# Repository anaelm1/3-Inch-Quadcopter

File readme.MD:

# 3-Inch Quadcopter

The quadcopter is a beginner-friendly drone built with a custom PCB and a custom 3D-printed body. 

The inspiration behind this project was to reignite the interest in drones I had when I was younger, and it will also be as a showcase project for my intended majors (mechanical and aeronautical engineering). Beyond this, the project is part of a idea of building autonomous delivery drones.

## Features
-  Custom PCB featuring an ESP32-C3 development board and a GY-521 IMU (gyroscope/accelerometer).
- Uses high-efficiency MOSFETs to drive the motors.
- Fully controllable via smartphone using the official ESP-Drone application over Wi-Fi.
- Designed with a 2:1 thrust-to-weight ratio to allow for snappy punch-outs.
- Balanced 3D-printed PETG X frame.

## CAD Model
The PCB is secured to the base plate using four M3 screws, with the battery fastened underneath using a Velcro strap. Cutouts on the base plate act as heat sinks for the MOSFETs. My name is embossed on the top plate.

*Designed in Autodesk Fusion 360.*

## PCB
The custom PCB was designed in KiCad. Power traces are wider  to safely handle high current loads. The board dimensions are 70mm × 70mm cuz I avoided surface mount components.

### Schematic

### PCB Layout

### 3D Render

## Firmware Overview
The firmware is written in the Arduino IDE. It implements a deterministic PID control loop and Wi-Fi initialization to work with the ESP-Drone mobile app.

## AI Usage
While I tried to keep AI use to a minimum, AI tools were utilized for:
- Researching and finalizing all electronic components.
- Helping with the firmware architecture.

## Experience
Building this project has been an incredible learning experience. I gained knowledge abou power electronics e.g capacitors, MOSFETs, and circuit protection. There were multiple design pivots throughout the development process (documented in `journal.md`). What I originally planned as a straightforward wiring exercise of connecting motors, an ESP32-C3, and a gyro truned into designing a detailed, PCB with over 30 components. Learning how to read manufacturer datasheets and apply them directly to hardware design was one of the most valuable takeaways of the project.

---

## Bill of Materials (BOM)

| Part | Type | Quantity | Unit price (USD) | Line total (USD) | Link | Vendor | Funding | Notes | CART |
| :--- | :--- | :---: | :---: | :---: | :--- | :--- | :--- | :--- | :--- |
| XT30U Male/Female Connectors (5 Pairs) | Part | 1 | $1.12 | $1.12 | https://s.click.aliexpress.com/e/_c3889eTv | Shop1105163493 Store | Grant | | AliExpress |
| 1W Metal Film Resistor 100 Ohm (20pcs pack) | Part | 1 | $1.97 | $1.97 | https://s.click.aliexpress.com/e/_c3E3aj0J | FXI Electronics Co. Ltd. Store | Grant | Lowest quantity sold together | AliExpress |
| 1W Metal Film Resistor 4.7K Ohm (20pcs pack) | Part | 1 | $1.94 | $1.94 | https://s.click.aliexpress.com/e/_c4SeKWnt | FXI Electronics Co. Ltd. Store | Grant | Lowest quantity sold together | AliExpress |
| 1W Metal Film Resistor 1K Ohm (20pcs pack) | Part | 1 | $1.97 | $1.97 | https://s.click.aliexpress.com/e/_c3FJaONV | FXI Electronics Co. Ltd. Store | Grant | Lowest quantity sold together | AliExpress |
| 75mm 2-Blade Propellers 4 Pairs | Part | 1 | $2.40 | $2.40 | https://s.click.aliexpress.com/e/_c3Jr3oTh | RC Club Store | Grant | | AliExpress |
| M3x5mm Nylon Pan Head Screws (50pcs pack) | Part | 1 | $0.93 | $0.93 | https://www.aliexpress.com/item/1005003145381687.html?spm=a2g0o.cart.0.0.e6cc38daaiHVPw&mp=1&pdp_npi=6%40dis%21USD%21USD+0.98%21USD+0.93%21%21USD+0.93%21%21%21%400be71e1917946913243825978e105e%2112000024341162464%21ct%21PK%216665188549%21%211%210%21 | HZYUEGOU SCREWHOME Store | Grant | Lowest quantity sold together | AliExpress |
| 16V 470uF Electrolytic Capacitor (5pcs pack) | Part | 1 | $1.83 | $1.83 | https://s.click.aliexpress.com/e/_c3mb84rh | shenzhenYida Store | Grant | Lowest quantity sold together | AliExpress |
| 16V 47uF Electrolytic Capacitor (5pcs pack) | Part | 1 | $1.69 | $1.69 | https://s.click.aliexpress.com/e/_c3Ba7dwL | shenzhenYida Store | Grant | Lowest quantity sold together | AliExpress |
| ESP32-C3 SuperMini Development Board | Part | 1 | $2.96 | $2.96 | https://www.aliexpress.com/item/1005008815113485.html?spm=a2g0o.cart.0.0.e6cc38daaiHVPw&mp=1&pdp_npi=6%40dis%21USD%21USD+3.96%21USD+2.96%21%21USD+2.96%21%21%21%400be71e1917946913243825978e105e%2112000053564399094%21ct%21PK%216665188549%21%211%210%21 | Shop1104003965 Store | Grant | | AliExpress |
| SS54 SMA SMD Rectifier Diode (50pcs pack) | Part | 1 | $1.91 | $1.91 | https://s.click.aliexpress.com/e/_c3g7i4M7 | Shop1103320155 Store | Grant | Lowest quantity sold together | AliExpress |
| IRF3708 TO-220 N-Channel MOSFET (10pcs pack) | Part | 1 | $3.49 | $3.49 | https://s.click.aliexpress.com/e/_c3twfGQB | Shop1105738136 Store | Grant | Lowest quantity sold together | AliExpress |
| 100nF Monolithic Ceramic Capacitor (100pcs pack) | Part | 1 | $1.78 | $1.78 | https://www.aliexpress.com/item/1135571256.html?spm=a2g0o.cart.0.0.e6cc38daaiHVPw&mp=1&pdp_npi=6%40dis%21USD%21USD+2.03%21USD+1.78%21%21USD+1.78%21%21%21%400be71e1917946913282516061e105e%2165192300108%21ct%21PK%216665188549%21%211%210%21 | Chinese Super Electronic market | Grant | Lowest quantity sold together | AliExpress |
| 5mm Assorted LED Diode Kit (100pcs total) | Part | 1 | $2.40 | $2.40 | https://www.aliexpress.com/item/1005003395932705.html?spm=a2g0o.cart.0.0.e6cc38daaiHVPw&mp=1&pdp_npi=6%40dis%21USD%21USD+2.78%21USD+2.40%21%21USD+2.40%21%21%21%400be71e1917946913282516061e105e%2112000025597631785%21ct%21PK%216665188549%21%211%210%21 | Pingtoudidi Store | Grant | Lowest quantity sold together | AliExpress |
| 5x20mm PCB Fuse Holder + 10A Fuse (10pcs pack) | Part | 1 | $2.15 | $2.15 | https://s.click.aliexpress.com/e/_c3f8mbJ5 | Ali_CanHui Store | Grant | Lowest quantity sold together | AliExpress |
| 1020 Coreless Motor 3.7V 54000RPM (2pcs pack) | Part | 3 | $3.70 | $11.10 | https://s.click.aliexpress.com/e/_c3aOOkLv | Motor Tool Part Store | Grant | Lowest quantity sold together | AliExpress |
| TPS61023 5V 1A Step-Up Boost Module | Part | 1 | $4.25 | $4.25 | https://s.click.aliexpress.com/e/_c3d6elGB | pb Peggybuy Official Store | Grant | | AliExpress |
| GY-521 MPU-6050 3-Axis Gyro/Accelerometer | Part | 1 | $4.85 | $4.85 | https://s.click.aliexpress.com/e/_c4BQ26QB | Shop1105442666 Store | Grant | | AliExpress |
| GNB TERANTY 1S 720mAh 3.8V 80C LiHV Battery | Part | 1 | $5.39 | $5.39 | https://s.click.aliexpress.com/e/_c31hyBf5 | GAONENG GNB BATTERY Store | Grant | | AliExpress |
| Tax | Tax or fee | 1 | $30.00 | $30.00 | | Customs | Grant | Tax | AliExpress |
| PCB | PCB | 1 | $18.00 | $18.00 | | JLCPCB | Grant | 4 for the board + 14 for the shipping (Cheapest possible) | JLCPCB |
| 3D printed body | 3D printed | 1 | $9.00 | $9.00 | | | Grant | The closest printing legion to me is in Singapore which costs a lot in shipping. That's why purchasing locally is cheaper | |
| AliExpress shipping | Shipping | 1 | $4.00 | $4.00 | | AliExpress | Grant | Most of my items are under free shipping but the battery doesn't have it | AliExpress |
| **Total** | | | | **$115.13** | | | | | |

---

## Info
This project was built for **Fabricate Hack Club**. Any feedback would be appreciated!

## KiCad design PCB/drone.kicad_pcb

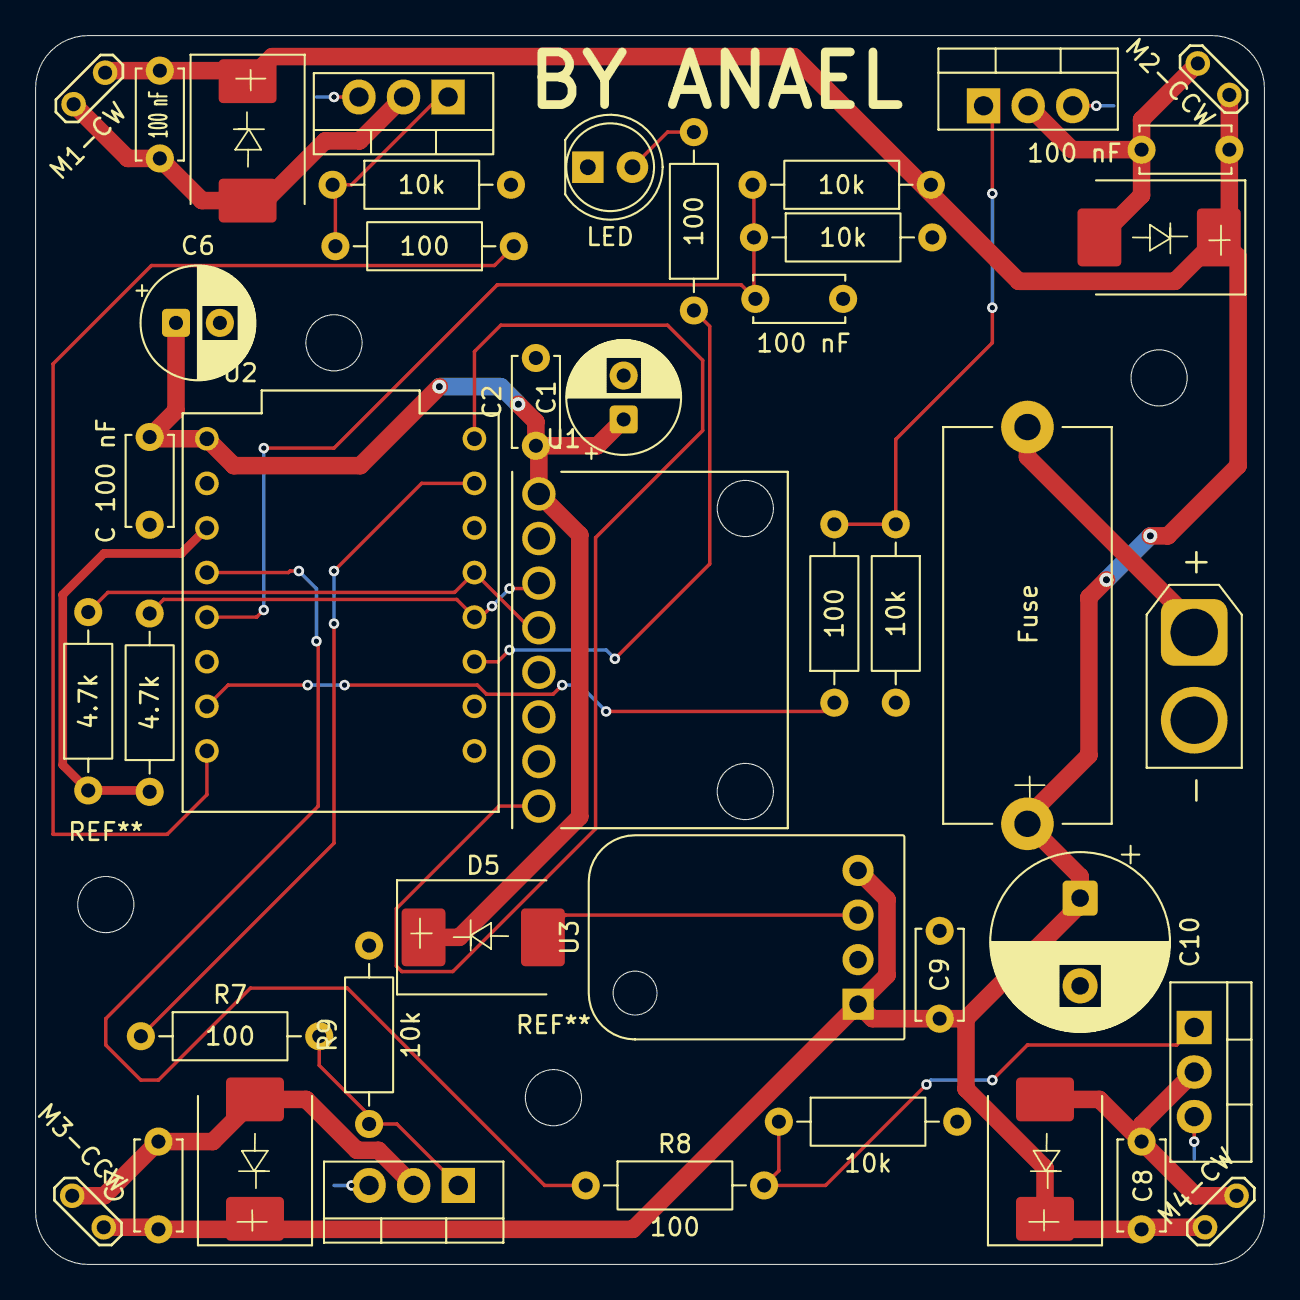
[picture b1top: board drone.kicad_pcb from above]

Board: 2 copper layers, 70.0 x 70.0 mm, 43 parts (0 on the bottom side), 24 nets.

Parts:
100 nF: C 100 nF; C_Disc_D5.0mm_W2.5mm_P5.00mm
C1, C6: C_Polarized 47UF; CP_Radial_D6.3mm_P2.50mm
C2, C5, C7, C8, C9: C 100 nF; C_Disc_D5.0mm_W2.5mm_P5.00mm
C4, C11: 100 nF; C_Disc_D5.0mm_W2.5mm_P5.00mm
C10: C_Polarized 470 UF; CP_Radial_D10.0mm_P5.00mm
D1, D2, D3, D4, D5: D_Schottky; D_SMC
D6: LED; LED_D5.0mm
F1: Fuse; Fuseholder_Cylinder-5x20mm_Stelvio-Kontek_PTF78_Horizontal_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
J1: Battery Connector; AMASS_XT30U-M_1x02_P5.0mm_Vertical
M1-CW, M2-CCW, M3-CCW, M4-CW: Motor_DC; TestPoint_2Pads_Pitch2.54mm_Drill0.8mm
Q5, Q6, Q7, Q8: Q_NMOS_GDS; TO-220-3_Vertical
R1, R2, R7, R8, R11: 100; R_Axial_DIN0207_L6.3mm_D2.5mm_P10.16mm_Horizontal
R3, R4, R9, R10, R12, R13: 10k; R_Axial_DIN0207_L6.3mm_D2.5mm_P10.16mm_Horizontal
R5, R6: 4.7k; R_Axial_DIN0207_L6.3mm_D2.5mm_P10.16mm_Horizontal
U1: GY-521; MODULE_GY-521
U2: ESP32C3-SUPERMINI; MODULE_ESP32-C3_SUPERMINI_TH
U3: TPS61023; Adafruit_MiniBoost_TPS61023

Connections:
3V3+: R5.1, R6.1, U2.14 (3V3)
5V+: C1.1, C2.1, C5.1, C6.1, D5.1 (K), U1.VCC, U2.16 (5V)
/BAT Monitor: C11.1, R12.2, R13.1, U2.12 (GPIO3)
/INT: U1.INT, U2.1 (GPIO5)
/LED: R11.1, U2.6 (GPIO10)
/Motor 1: R2.1, U2.9 (GPIO0)
/Motor 2: R1.1, U2.10 (GPIO1)
/Motor 3: R7.1, U2.2 (GPIO6)
/Motor 4: R8.1, U2.13 (GPIO4)
/SCL: R6.2, U1.SCL, U2.5 (GPIO9)
BAT+: 100 nF.1, C4.1, C7.1, C8.1, C9.2, C10.1, D1.1 (K), D2.1 (K), D3.1 (K), D4.1 (K), F1.2, M1-CW.1 (+), M2-CCW.1 (+), M3-CCW.1 (+), M4-CW.1 (+), R12.1, U3.1 (VIN), U3.4 (En)
GND: C1.2, C2.2, C5.2, C6.2, C9.1, C10.2, C11.2, D6.1 (K), J1.2, Q5.3 (S), Q6.3 (S), Q7.3 (S), Q8.3 (S), R3.2, R4.2, R9.2, R10.2, R13.2, U1.AD0, U1.GND, U2.15 (GND), U3.2 (GND)
unnamed: 100 nF.2, D1.2 (A), M1-CW.2 (-), Q5.2 (D)
unnamed: C4.2, D2.2 (A), M2-CCW.2 (-), Q7.2 (D)
unnamed: C7.2, D3.2 (A), M3-CCW.2 (-), Q8.2 (D)
unnamed: C8.2, D4.2 (A), M4-CW.2 (-), Q6.2 (D)
unnamed: D5.2 (A), U3.3 (5v)
unnamed: D6.2 (A), R11.2
unnamed: F1.1, J1.1
unnamed: Q5.1 (G), R2.2, R3.1
unnamed: Q6.1 (G), R8.2, R10.1
unnamed: Q7.1 (G), R1.2, R4.1
unnamed: Q8.1 (G), R7.2, R9.1
unnamed: R5.2, U1.SDA, U2.4 (GPIO8)
